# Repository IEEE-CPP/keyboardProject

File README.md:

# Split Keyboard

A custom split ergonomic keyboard designed with Ergogen and KiCad.

## Keyboard Layout

- **5-column layout**: outer, pinky, ring, middle, index, inner
- **5 rows**: mod, bottom, home, top, num
- **3-thumb keys**: layer, space, extra
- **Column-based wiring** with row diodes

### Features

- Choc hotswap sockets (Kailh Choc low-profile switches)
- Pro Micro microcontroller (ATmega32U4)
- OLED displays (SSD1306, I2C)
- TRRS jack for inter-board communication
- ESD protection on TRRS data lines
- Reset button
- 3D printable case files (STL)

## Files

```
splitKeyboard/
├── ergogen/
│   ├── config.yaml    # Ergogen configuration (layout, PCB definitions)
│   ├── footprints/    # Custom footprint definitions
│   └── output/
│       ├── cases/    # 3D printable case files (STL)
│       └── outlines/ # DXF files for CNC cutting
└── kicad/
    ├── left_board.kicad_pcb   # Left half PCB design
    └── right_board.kicad_pcb  # Right half PCB design
```

## Development Setup

### Manual (recommended)

Install ergogen from https://ergogen.xyz/install/, then generate PCBs:

```bash
ergogen splitKeyboard/ergogen/ --output build/
```

### Nix (optional)

For users with Nix installed:

```bash
nix develop    # provides kicad + ergogen
generate       # runs ergogen (PCB + cases) and organizes output
```

## Design Details

- **Microcontroller**: Pro Micro (5V, 16MHz)
- **Key switches**: Kailh Choc (low-profile)
- **Diodes**: 1N4148 (or similar)
- **OLED**: SSD1306 128x32 I2C
- **Interconnect**: TRRS cable (4-pole)
- **ESD Protection**: TVS diodes (PRTR5V0U2X or similar)

### Pin Mapping

| Column | Pin |
| ------ | --- |
| outer  | P21 |
| pinky  | P20 |
| ring   | P19 |
| middle | P18 |
| index  | P15 |
| inner  | P14 |
| thumb  | P16 |
| space  | P10 |
| extra  | P9  |

| Row    | Pin |
| ------ | --- |
| mod    | P8  |
| bottom | P7  |
| home   | P6  |
| top    | P5  |
| num    | P4  |

### OLED

- SDA: P2
- SCL: P3

## Building

1. Generate PCB files (see Development Setup above)

2. Open `splitKeyboard/kicad/` in KiCad to generate Gerbers

3. Order PCBs from your preferred manufacturer

4. Solder components:
   - Diodes (observe polarity)
   - Hotswap sockets
   - TRRS jack
   - Reset button
   - OLED display
   - Pro Micro header pins (or socket)

5. Flash firmware using QMK or ZMK

## Firmware

This repository only contains the hardware design. For firmware, use:

- **QMK**: https://github.com/qmk/qmk_firmware
- **ZMK**: https://github.com/zmkfirmware/zmk

## License

GNU General Public License v3. See [LICENSE](LICENSE) for details.

## Credits

- [Ergogen](https://github.com/ergogen/ergogen) - Keyboard layout generator
- [KiCad](https://www.kicad.org/) - PCB design software

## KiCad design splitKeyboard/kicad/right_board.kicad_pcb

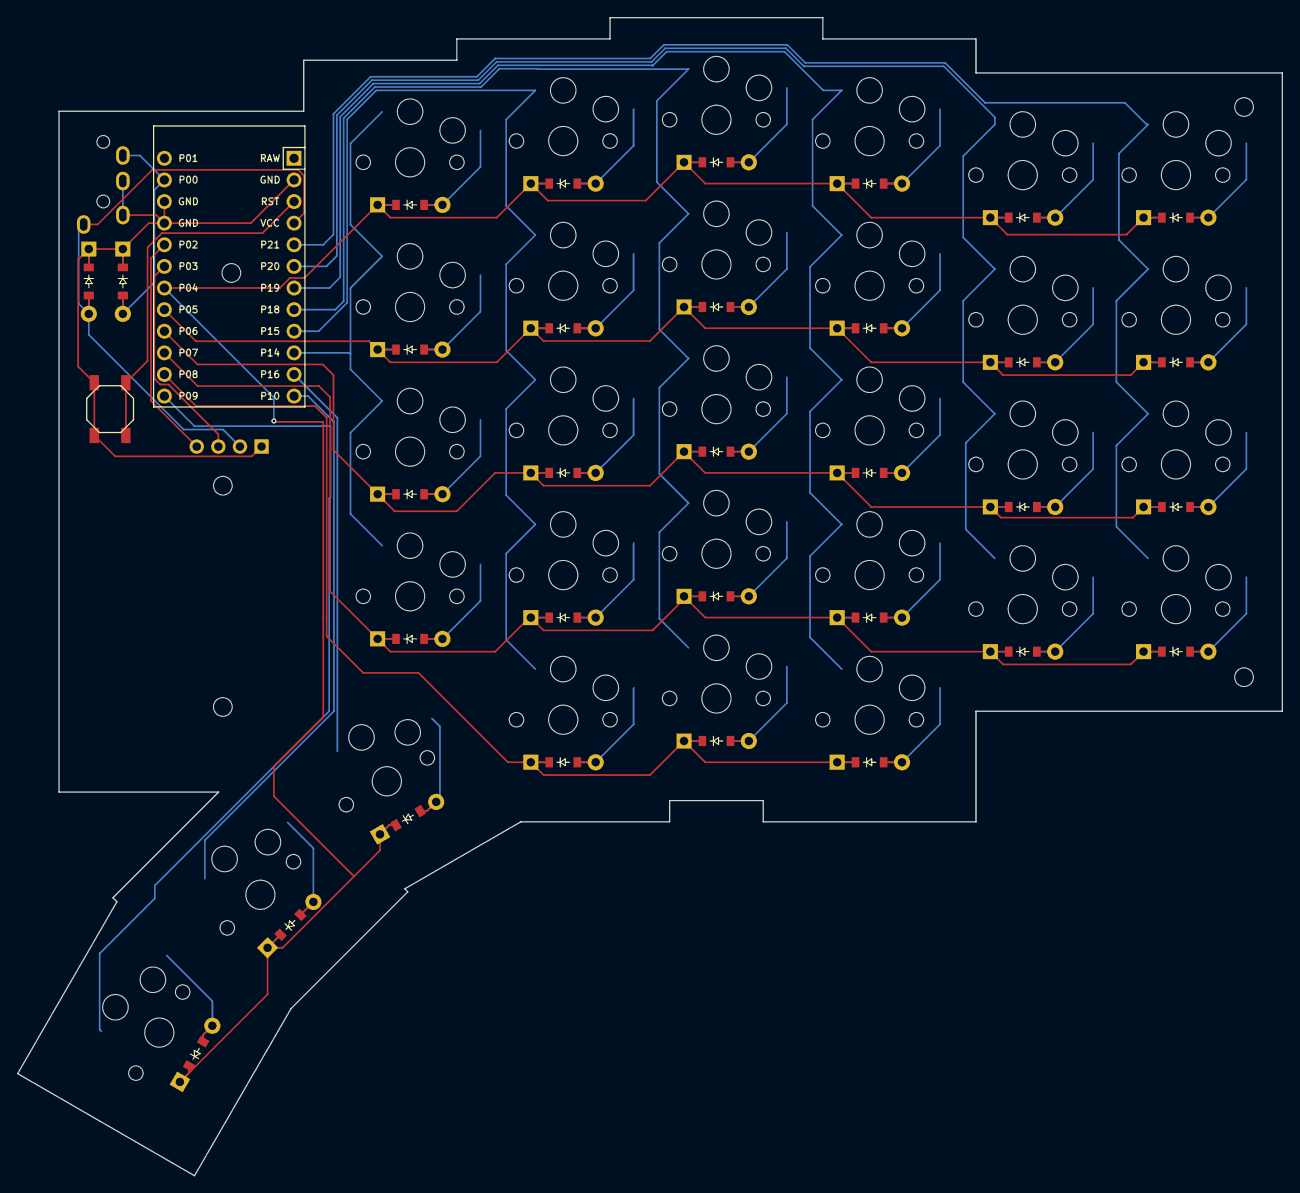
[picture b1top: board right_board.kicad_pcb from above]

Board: 2 copper layers, 148.6 x 136.1 mm, 71 parts (0 on the bottom side), 50 nets.

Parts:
B1: SW_TACT_ALPS_SKQGABE010
D1, D2, D3, D4, D5, D6, D7, D8, D9, D10, D11, D12, D13, D14, D15, D16, D17, D18, D19, D20, D21, D22, D23, D24, D25, D26, D27, D28, D29, D30, D31, D32: ComboDiode
MCU1: ProMicro
MH1, MH2, MH3, MH4, MH5: mounting_hole_npth
OLED1: OLED; OLED_headers
S1, S2, S3, S4, S5, S6, S7, S8, S9, S10, S11, S12, S13, S14, S15, S16, S17, S18, S19, S20, S21, S22, S23, S24, S25, S26, S27, S28, S29, S30: PG1350
TRRS1: TRRS-PJ-320A-dual

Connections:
GND: B1.1, D31.1, D32.1, MCU1.2, MCU1.15, MCU1.16, OLED1.1, TRRS1.2, TRRS1.3
P0: D31.2, MCU1.14, TRRS1.4
P2: MCU1.17, OLED1.4
P3: MCU1.18, OLED1.3
P4: D4.1, D8.1, D13.1, D18.1, D23.1, D27.1, D28.1, D29.1, D30.1, MCU1.19
P5: D3.1, D7.1, D12.1, D17.1, D22.1, D26.1, MCU1.20
P6: D2.1, D6.1, D11.1, D16.1, D21.1, D25.1, MCU1.21
P7: D1.1, D5.1, D10.1, D15.1, D20.1, D24.1, MCU1.22
P8: D9.1, D14.1, D19.1, MCU1.23
P9: MCU1.24, S30.1
P10: MCU1.12, S29.1
P14: MCU1.10, S24.1, S25.1, S26.1, S27.1
P15: MCU1.9, S19.1, S20.1, S21.1, S22.1, S23.1
P16: MCU1.11, S28.1
P18: MCU1.8, S14.1, S15.1, S16.1, S17.1, S18.1
P19: MCU1.7, S9.1, S10.1, S11.1, S12.1, S13.1
P20: MCU1.6, S5.1, S6.1, S7.1, S8.1
P21: MCU1.5, S1.1, S2.1, S3.1, S4.1
RST: B1.2, MCU1.3
VCC: D32.2, MCU1.4, OLED1.2, TRRS1.1
mirror_extra_cluster: D30.2, S30.2
mirror_index_bottom: D20.2, S20.2
mirror_index_home: D21.2, S21.2
mirror_index_mod: D19.2, S19.2
mirror_index_num: D23.2, S23.2
mirror_index_top: D22.2, S22.2
mirror_inner_bottom: D24.2, S24.2
mirror_inner_home: D25.2, S25.2
mirror_inner_num: D27.2, S27.2
mirror_inner_top: D26.2, S26.2
mirror_layer_cluster: D28.2, S28.2
mirror_middle_bottom: D15.2, S15.2
mirror_middle_home: D16.2, S16.2
mirror_middle_mod: D14.2, S14.2
mirror_middle_num: D18.2, S18.2
mirror_middle_top: D17.2, S17.2
mirror_outer_bottom: D1.2, S1.2
mirror_outer_home: D2.2, S2.2
mirror_outer_num: D4.2, S4.2
mirror_outer_top: D3.2, S3.2
mirror_pinky_bottom: D5.2, S5.2
mirror_pinky_home: D6.2, S6.2
mirror_pinky_num: D8.2, S8.2
mirror_pinky_top: D7.2, S7.2
mirror_ring_bottom: D10.2, S10.2
mirror_ring_home: D11.2, S11.2
mirror_ring_mod: D9.2, S9.2
mirror_ring_num: D13.2, S13.2
mirror_ring_top: D12.2, S12.2
mirror_space_cluster: D29.2, S29.2

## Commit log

2026-03-12 feat(splitKeyboard): added splitKeyboard ergogen config
2026-03-26 updated ergogen yaml
2026-03-26 chore(nix): switched to using dev shell and added ergogen
2026-03-26 chore(gitignore): setup gitignore
2026-03-26 chore(ergogen): gave ergogen stuff its own directory
2026-03-27 chore(nix): added generate command to automate pcb movement
2026-03-27 chore(ergogen): added ceoloide's footprints
2026-03-27 feat(board): mounting points and case
2026-03-27 fix: got rid of unnecessary extra side
2026-03-27 feat(case): increased wall height
2026-03-27 docs: updated readme
2026-03-29 feat(left_board): left_board traced
2026-03-29 feat(right_board): right board traced
